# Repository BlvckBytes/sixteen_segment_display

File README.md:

# sixteen_segment_display

## PCB

### display_group

Four sixteen segment displays are considered to be a group.

### interface

The interface board drives a display group by converting the serial signal into all sixteen segments, including the decimal point, as well as each display's enabled state.

### driver

Has yet to be implemented.

The driver board resembles the bridge between modern devices and the display while also handling the process of detecting the total number of displays, handling the character decoding process, multiplexing displays and playing various animations, like blinking letters or scrolling text.

## Software

### SegmentStates

This project encodes all available segment states in order to display various characters. A decoding table is then generated from this information.

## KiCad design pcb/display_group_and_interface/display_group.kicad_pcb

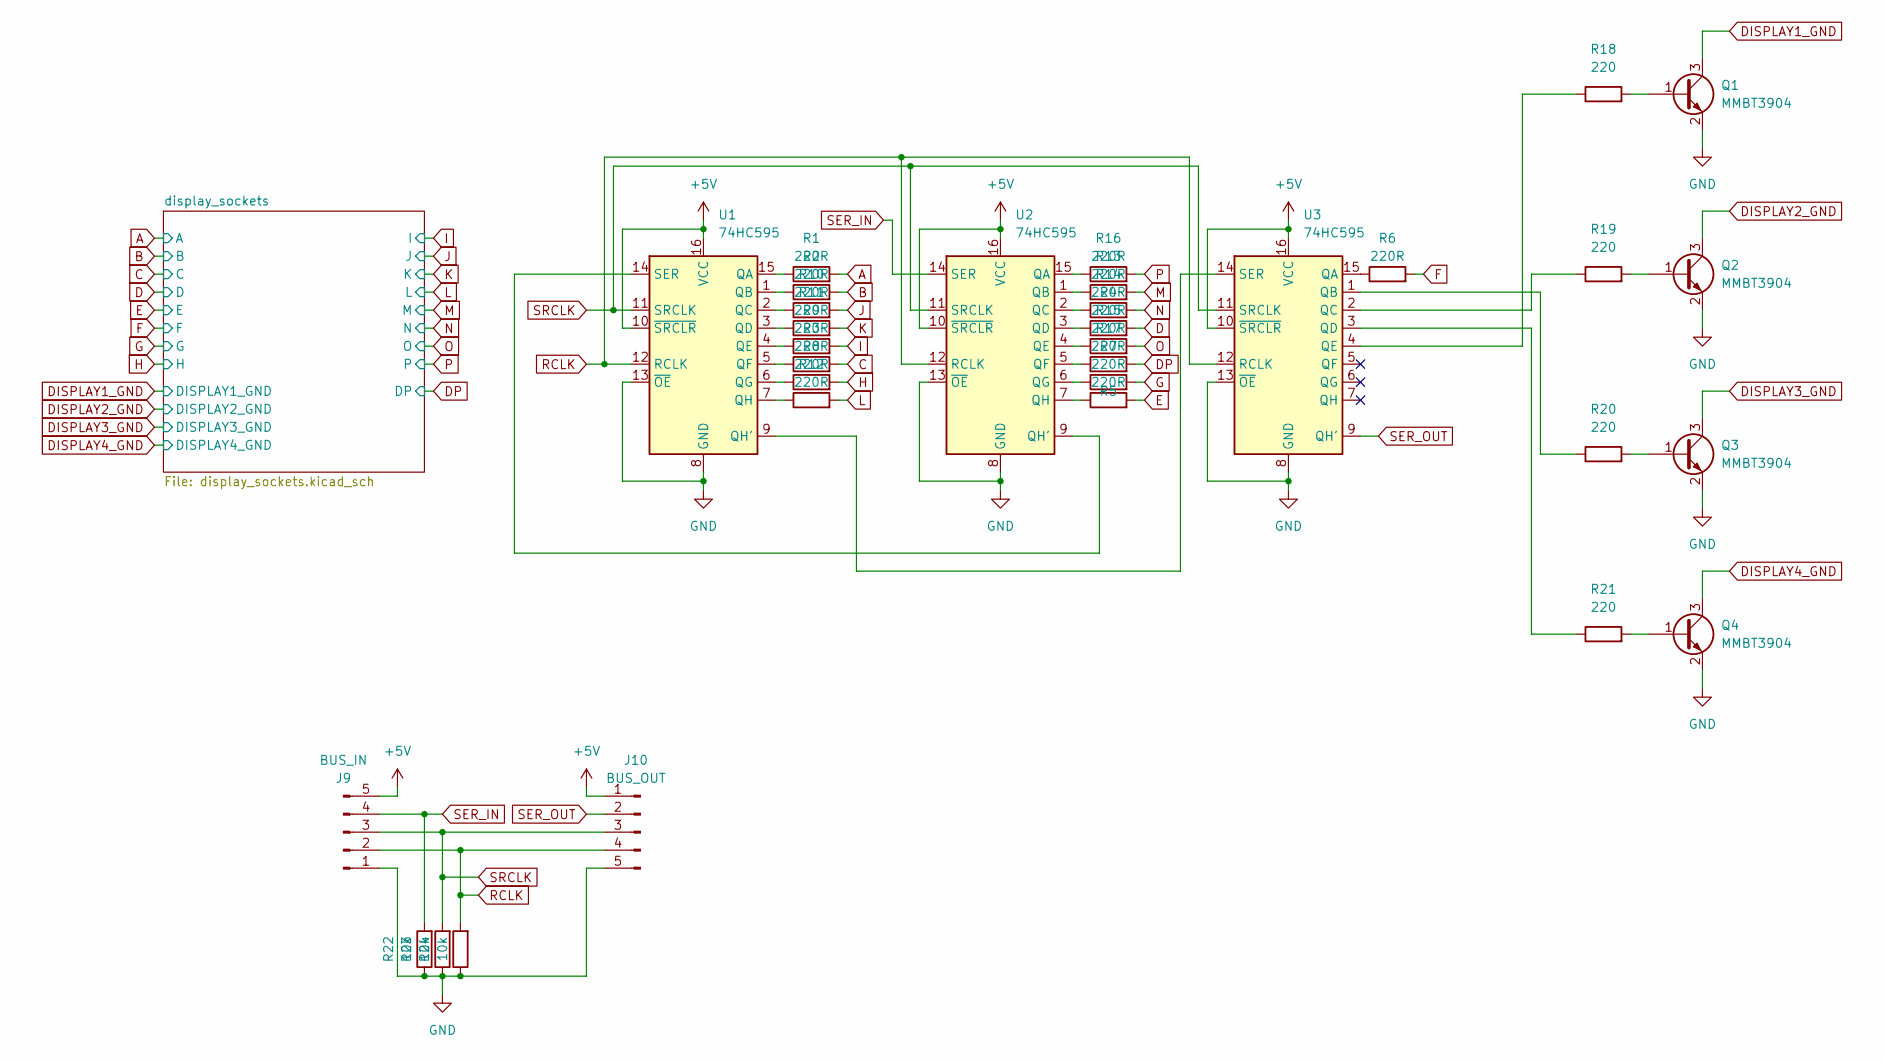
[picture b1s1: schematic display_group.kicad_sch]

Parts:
J9: BUS_IN; PinHeader_01x05_P2.54mm_Horizontal_SMDified
J10: BUS_OUT; PinHeader_01x05_P2.54mm_Horizontal_SMDified
Q1, Q2, Q3, Q4: MMBT3904; SOT-23
R1, R2, R3, R4, R5, R6, R7, R8, R9, R10, R11, R12, R13, R14, R15, R16, R17: 220R; R_0603_1608Metric
R18, R19, R20, R21: 220; R_0603_1608Metric
R22, R23, R24: 10k; R_0603_1608Metric
U1, U2, U3: 74HC595; SOIC-16_3.9x9.9mm_P1.27mm

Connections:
+5V: J9.5, J10.1, U1.10 (~SRCLR), U1.16 (VCC), U2.10 (~SRCLR), U2.16 (VCC), U3.10 (~SRCLR), U3.16 (VCC)
A: R1.2; also elsewhere on the board
B: R2.2; also elsewhere on the board
C: R3.2; also elsewhere on the board
D: R4.2; also elsewhere on the board
DISPLAY1_GND: Q1.3 (C); also elsewhere on the board
DISPLAY2_GND: Q2.3 (C); also elsewhere on the board
DISPLAY3_GND: Q3.3 (C); also elsewhere on the board
DISPLAY4_GND: Q4.3 (C); also elsewhere on the board
DP: R17.2; also elsewhere on the board
E: R5.2; also elsewhere on the board
F: R6.2; also elsewhere on the board
G: R7.2; also elsewhere on the board
GND: J9.1, J10.5, Q1.2 (E), Q2.2 (E), Q3.2 (E), Q4.2 (E), R22.1, R23.1, R24.1, U1.8 (GND), U1.13 (~OE), U2.8 (GND), U2.13 (~OE), U3.8 (GND), U3.13 (~OE)
H: R8.2; also elsewhere on the board
I: R9.2; also elsewhere on the board
J: R10.2; also elsewhere on the board
K: R11.2; also elsewhere on the board
L: R12.2; also elsewhere on the board
M: R13.2; also elsewhere on the board
N: R14.2; also elsewhere on the board
unnamed: Q1.1 (B), R18.2
unnamed: Q2.1 (B), R19.2
unnamed: Q3.1 (B), R20.2
unnamed: Q4.1 (B), R21.2
unnamed: R1.1, U1.15 (QA)
unnamed: R2.1, U1.1 (QB)
unnamed: R10.1, U1.2 (QC)
unnamed: R11.1, U1.3 (QD)
unnamed: R9.1, U1.4 (QE)
unnamed: R3.1, U1.5 (QF)
unnamed: R8.1, U1.6 (QG)
unnamed: U1.9 (QH'), U3.14 (SER)
unnamed: R12.1, U1.7 (QH)
unnamed: U1.14 (SER), U2.9 (QH')
unnamed: R16.1, U2.15 (QA)
unnamed: R13.1, U2.1 (QB)
unnamed: R14.1, U2.2 (QC)
unnamed: R4.1, U2.3 (QD)
unnamed: R15.1, U2.4 (QE)
unnamed: R17.1, U2.5 (QF)
unnamed: R7.1, U2.6 (QG)
unnamed: R5.1, U2.7 (QH)
unnamed: R6.1, U3.15 (QA)
unnamed: R20.1, U3.1 (QB)
unnamed: R19.1, U3.2 (QC)
unnamed: R21.1, U3.3 (QD)
unnamed: R18.1, U3.4 (QE)
O: R15.2; also elsewhere on the board
P: R16.2; also elsewhere on the board
RCLK: J9.2, J10.4, R24.2, U1.12 (RCLK), U2.12 (RCLK), U3.12 (RCLK)
SER_IN: J9.4, R22.2, U2.14 (SER)
SER_OUT: J10.2, U3.9 (QH')
SRCLK: J9.3, J10.3, R23.2, U1.11 (SRCLK), U2.11 (SRCLK), U3.11 (SRCLK)

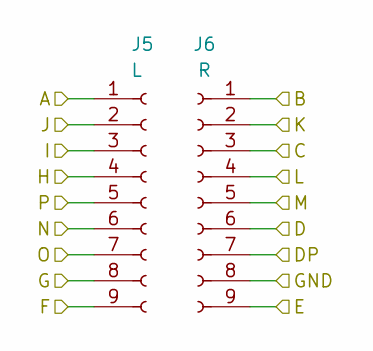
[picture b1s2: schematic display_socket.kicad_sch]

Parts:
J5: L; PinSocket_1x09_P2.54mm_Vertical_SMD_Pin1Right
J6: R; PinSocket_1x09_P2.54mm_Vertical_SMD_Pin1Right

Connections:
A: J5.1; also elsewhere on the board
B: J6.1; also elsewhere on the board
C: J6.3; also elsewhere on the board
D: J6.6; also elsewhere on the board
DISPLAY3_GND: J6.8; also elsewhere on the board
DP: J6.7; also elsewhere on the board
E: J6.9; also elsewhere on the board
F: J5.9; also elsewhere on the board
G: J5.8; also elsewhere on the board
H: J5.4; also elsewhere on the board
I: J5.3; also elsewhere on the board
J: J5.2; also elsewhere on the board
K: J6.2; also elsewhere on the board
L: J6.4; also elsewhere on the board
M: J6.5; also elsewhere on the board
N: J5.6; also elsewhere on the board
O: J5.7; also elsewhere on the board
P: J5.5; also elsewhere on the board

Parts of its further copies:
J1, J3, J7: L; PinSocket_1x09_P2.54mm_Vertical_SMD_Pin1Right
J2, J4, J8: R; PinSocket_1x09_P2.54mm_Vertical_SMD_Pin1Right

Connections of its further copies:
A: J1.1, J3.1, J7.1; also elsewhere on the board
B: J2.1, J4.1, J8.1; also elsewhere on the board
C: J2.3, J4.3, J8.3; also elsewhere on the board
D: J2.6, J4.6, J8.6; also elsewhere on the board
DISPLAY1_GND: J8.8; also elsewhere on the board
DISPLAY2_GND: J2.8; also elsewhere on the board
DISPLAY4_GND: J4.8; also elsewhere on the board
DP: J2.7, J4.7, J8.7; also elsewhere on the board
E: J2.9, J4.9, J8.9; also elsewhere on the board
F: J1.9, J3.9, J7.9; also elsewhere on the board
G: J1.8, J3.8, J7.8; also elsewhere on the board
H: J1.4, J3.4, J7.4; also elsewhere on the board
I: J1.3, J3.3, J7.3; also elsewhere on the board
J: J1.2, J3.2, J7.2; also elsewhere on the board
K: J2.2, J4.2, J8.2; also elsewhere on the board
L: J2.4, J4.4, J8.4; also elsewhere on the board
M: J2.5, J4.5, J8.5; also elsewhere on the board
N: J1.6, J3.6, J7.6; also elsewhere on the board
O: J1.7, J3.7, J7.7; also elsewhere on the board
P: J1.5, J3.5, J7.5; also elsewhere on the board

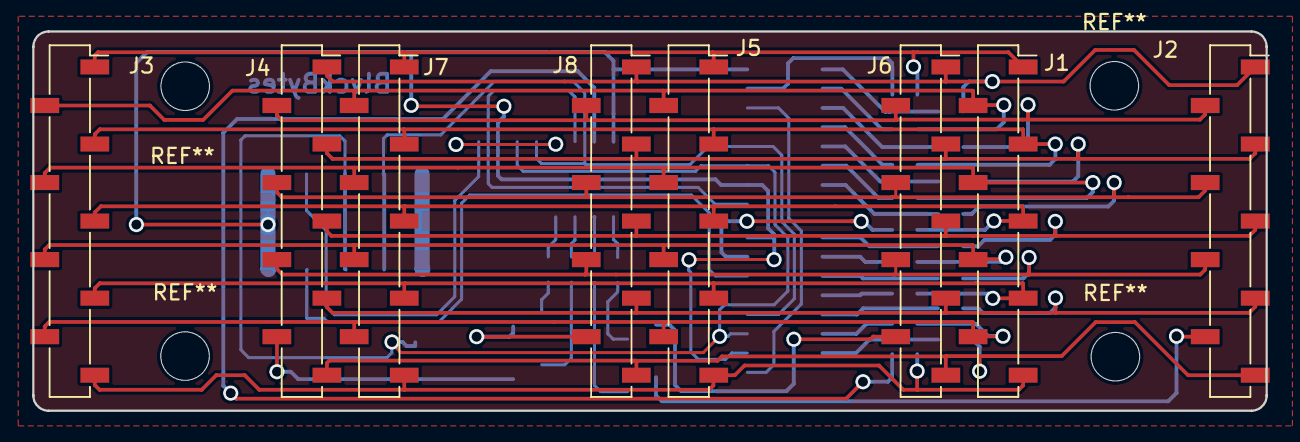
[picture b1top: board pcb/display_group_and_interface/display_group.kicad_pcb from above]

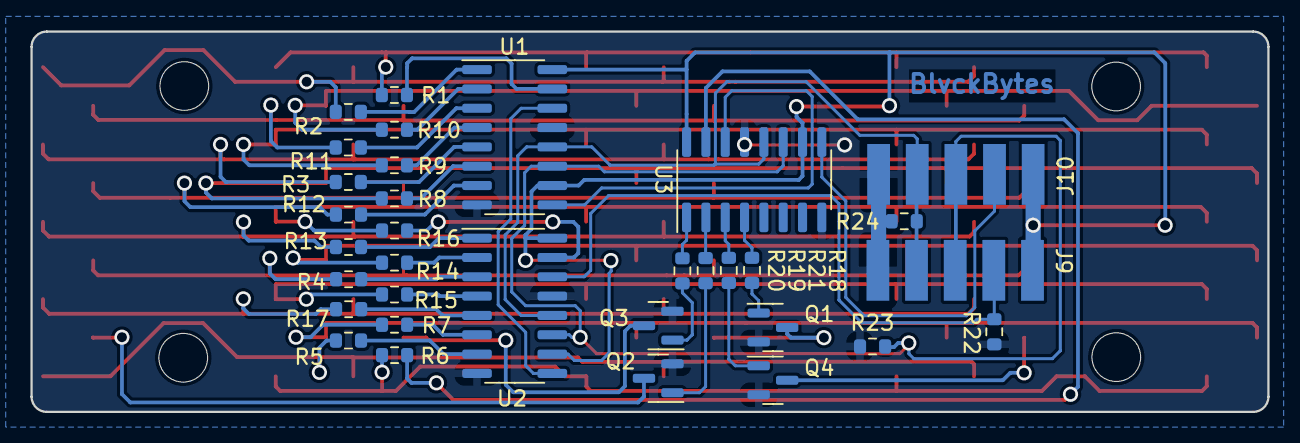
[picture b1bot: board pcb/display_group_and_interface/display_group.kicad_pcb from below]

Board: 2 copper layers, 81.3 x 25.0 mm, 41 parts (33 on the bottom side), 54 nets.

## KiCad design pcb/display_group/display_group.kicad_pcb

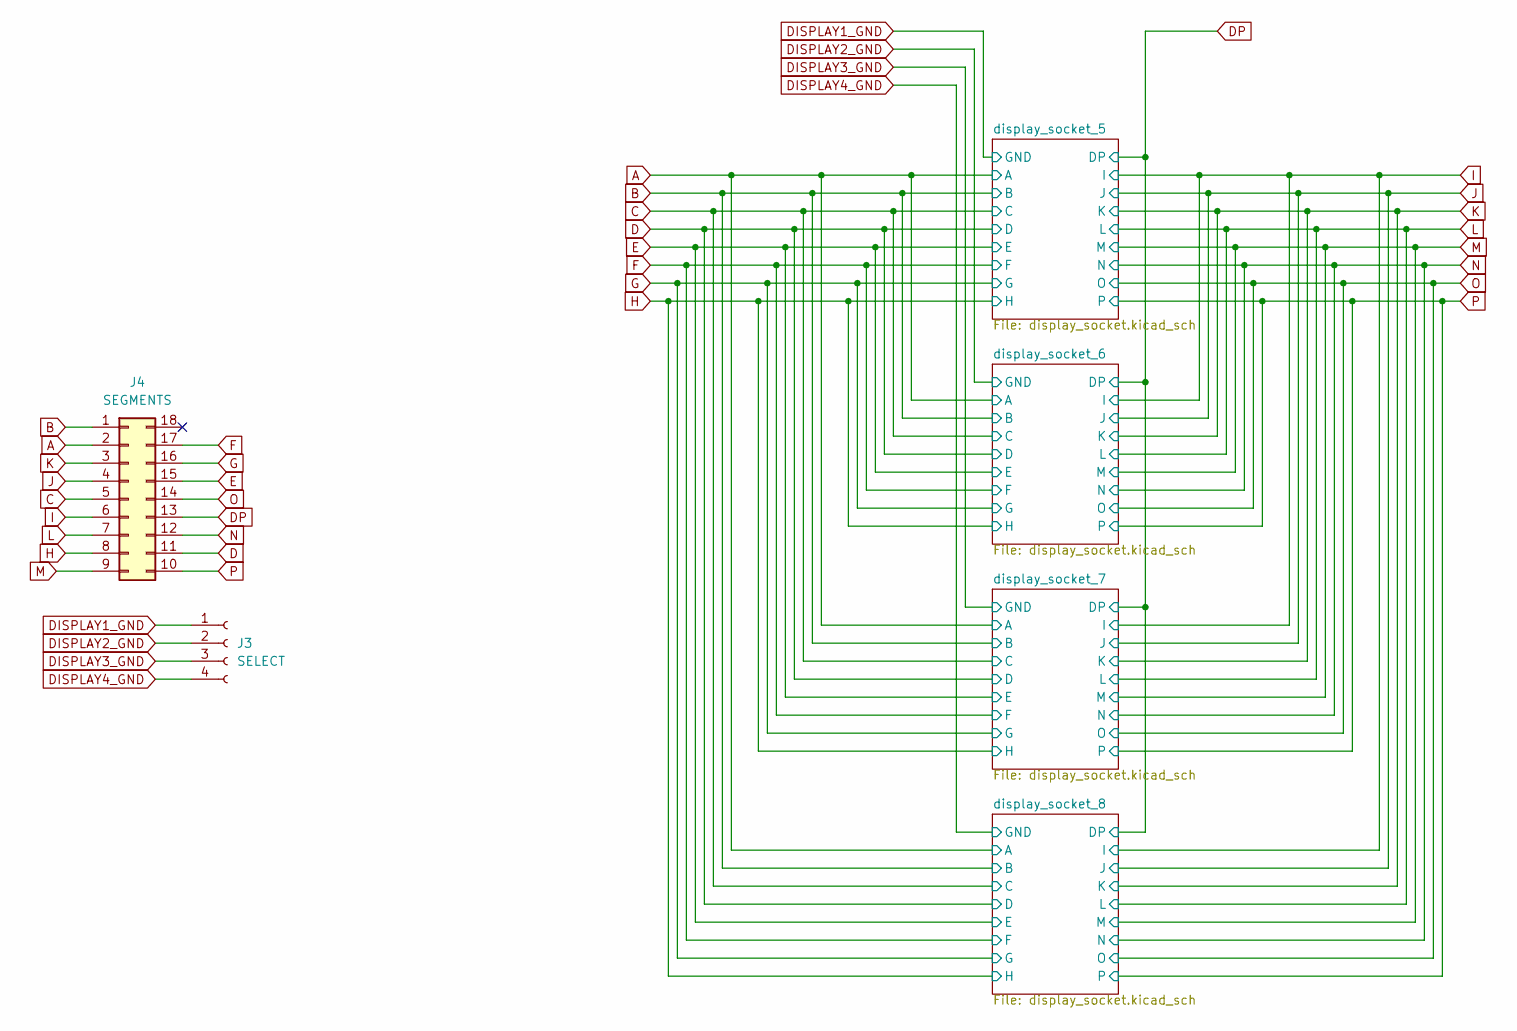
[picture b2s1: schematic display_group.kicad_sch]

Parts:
J3: SELECT; PinSocket_1x04_P2.54mm_Vertical_SMD_Pin1Left
J4: SEGMENTS; PinHeader_2x09_P2.54mm_Vertical

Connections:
A: J4.2; also elsewhere on the board
B: J4.1; also elsewhere on the board
C: J4.5; also elsewhere on the board
D: J4.11; also elsewhere on the board
DISPLAY1_GND: J3.1; also elsewhere on the board
DISPLAY2_GND: J3.2; also elsewhere on the board
DISPLAY3_GND: J3.3; also elsewhere on the board
DISPLAY4_GND: J3.4; also elsewhere on the board
DP: J4.13; also elsewhere on the board
E: J4.15; also elsewhere on the board
F: J4.17; also elsewhere on the board
G: J4.16; also elsewhere on the board
H: J4.8; also elsewhere on the board
I: J4.6; also elsewhere on the board
J: J4.4; also elsewhere on the board
K: J4.3; also elsewhere on the board
L: J4.7; also elsewhere on the board
M: J4.9; also elsewhere on the board
N: J4.12; also elsewhere on the board
O: J4.14; also elsewhere on the board
P: J4.10; also elsewhere on the board

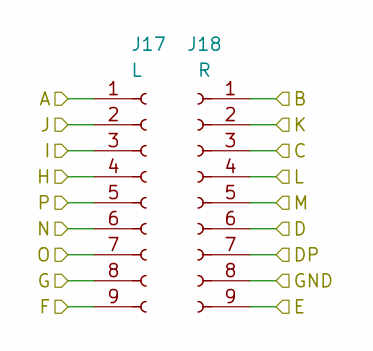
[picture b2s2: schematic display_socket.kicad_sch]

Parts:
J17: L; PinSocket_1x09_P2.54mm_Vertical_SMD_Pin1Right
J18: R; PinSocket_1x09_P2.54mm_Vertical_SMD_Pin1Right

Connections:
A: J17.1; also elsewhere on the board
B: J18.1; also elsewhere on the board
C: J18.3; also elsewhere on the board
D: J18.6; also elsewhere on the board
DISPLAY1_GND: J18.8; also elsewhere on the board
DP: J18.7; also elsewhere on the board
E: J18.9; also elsewhere on the board
F: J17.9; also elsewhere on the board
G: J17.8; also elsewhere on the board
H: J17.4; also elsewhere on the board
I: J17.3; also elsewhere on the board
J: J17.2; also elsewhere on the board
K: J18.2; also elsewhere on the board
L: J18.4; also elsewhere on the board
M: J18.5; also elsewhere on the board
N: J17.6; also elsewhere on the board
O: J17.7; also elsewhere on the board
P: J17.5; also elsewhere on the board

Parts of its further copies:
J1, J5, J7: L; PinSocket_1x09_P2.54mm_Vertical_SMD_Pin1Right
J2, J6, J16: R; PinSocket_1x09_P2.54mm_Vertical_SMD_Pin1Right

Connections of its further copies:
A: J1.1, J5.1, J7.1; also elsewhere on the board
B: J2.1, J6.1, J16.1; also elsewhere on the board
C: J2.3, J6.3, J16.3; also elsewhere on the board
D: J2.6, J6.6, J16.6; also elsewhere on the board
DISPLAY2_GND: J16.8; also elsewhere on the board
DISPLAY3_GND: J6.8; also elsewhere on the board
DISPLAY4_GND: J2.8; also elsewhere on the board
DP: J2.7, J6.7, J16.7; also elsewhere on the board
E: J2.9, J6.9, J16.9; also elsewhere on the board
F: J1.9, J5.9, J7.9; also elsewhere on the board
G: J1.8, J5.8, J7.8; also elsewhere on the board
H: J1.4, J5.4, J7.4; also elsewhere on the board
I: J1.3, J5.3, J7.3; also elsewhere on the board
J: J1.2, J5.2, J7.2; also elsewhere on the board
K: J2.2, J6.2, J16.2; also elsewhere on the board
L: J2.4, J6.4, J16.4; also elsewhere on the board
M: J2.5, J6.5, J16.5; also elsewhere on the board
N: J1.6, J5.6, J7.6; also elsewhere on the board
O: J1.7, J5.7, J7.7; also elsewhere on the board
P: J1.5, J5.5, J7.5; also elsewhere on the board

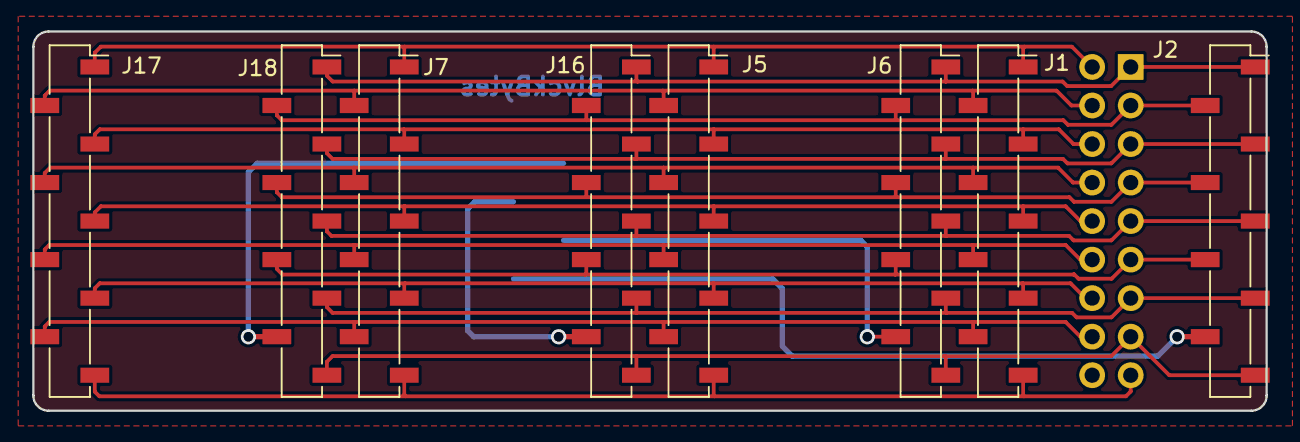
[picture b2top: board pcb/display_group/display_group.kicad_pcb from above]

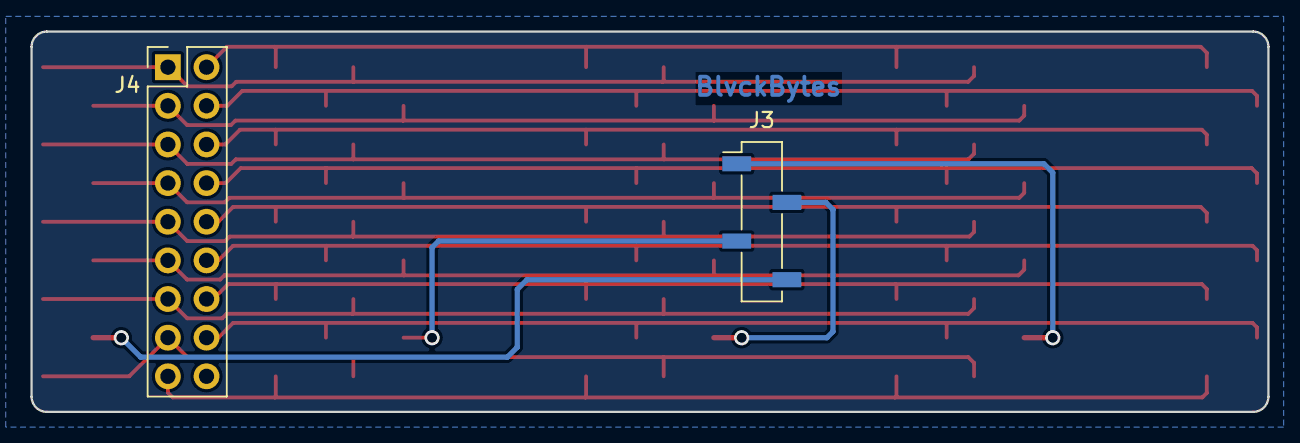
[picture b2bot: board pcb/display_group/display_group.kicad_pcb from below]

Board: 2 copper layers, 81.3 x 25.0 mm, 10 parts (2 on the bottom side), 21 nets.

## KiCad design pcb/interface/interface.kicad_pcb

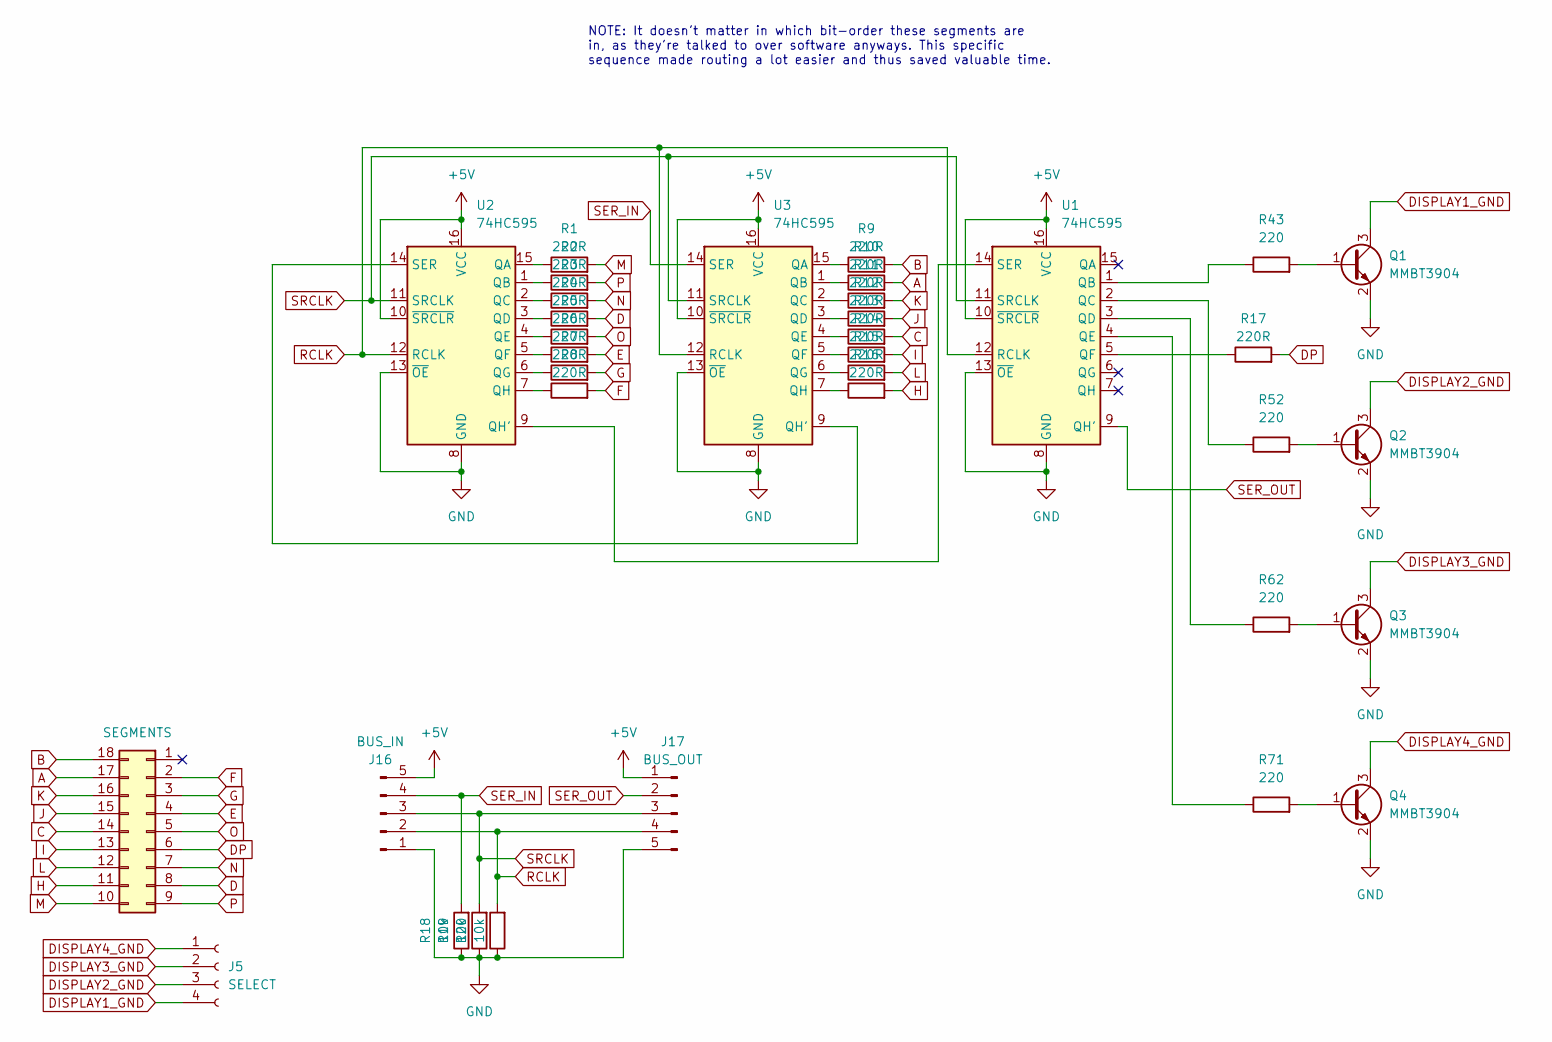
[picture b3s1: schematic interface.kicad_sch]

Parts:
J1: SEGMENTS; PinSocket_2x09_P2.54mm_Vertical
J5: SELECT; PinHeader_1x04_P2.54mm_Vertical
J16: BUS_IN; PinHeader_01x05_P2.54mm_Horizontal_SMDified
J17: BUS_OUT; PinHeader_01x05_P2.54mm_Horizontal_SMDified
Q1, Q2, Q3, Q4: MMBT3904; SOT-23
R1, R2, R3, R4, R5, R6, R7, R8, R9, R10, R11, R12, R13, R14, R15, R16, R17: 220R; R_0603_1608Metric
R18, R19, R20: 10k; R_0603_1608Metric
R43, R52, R62, R71: 220; R_0603_1608Metric
U1, U2, U3: 74HC595; SOIC-16_3.9x9.9mm_P1.27mm

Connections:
+5V: J16.5, J17.1, U1.10 (~SRCLR), U1.16 (VCC), U2.10 (~SRCLR), U2.16 (VCC), U3.10 (~SRCLR), U3.16 (VCC)
A: J1.17, R10.2
B: J1.18, R9.2
C: J1.14, R13.2
D: J1.8, R4.2
DISPLAY1_GND: J5.4, Q1.3 (C)
DISPLAY2_GND: J5.3, Q2.3 (C)
DISPLAY3_GND: J5.2, Q3.3 (C)
DISPLAY4_GND: J5.1, Q4.3 (C)
DP: J1.6, R17.2
E: J1.4, R6.2
F: J1.2, R8.2
G: J1.3, R7.2
GND: J16.1, J17.5, Q1.2 (E), Q2.2 (E), Q3.2 (E), Q4.2 (E), R18.1, R19.1, R20.1, U1.8 (GND), U1.13 (~OE), U2.8 (GND), U2.13 (~OE), U3.8 (GND), U3.13 (~OE)
H: J1.11, R16.2
I: J1.13, R14.2
J: J1.15, R12.2
K: J1.16, R11.2
L: J1.12, R15.2
M: J1.10, R1.2
N: J1.7, R3.2
unnamed: Q1.1 (B), R43.2
unnamed: Q2.1 (B), R52.2
unnamed: Q3.1 (B), R62.2
unnamed: Q4.1 (B), R71.2
unnamed: R43.1, U1.1 (QB)
unnamed: R52.1, U1.2 (QC)
unnamed: R62.1, U1.3 (QD)
unnamed: R71.1, U1.4 (QE)
unnamed: R17.1, U1.5 (QF)
unnamed: U1.14 (SER), U2.9 (QH')
unnamed: R1.1, U2.15 (QA)
unnamed: R2.1, U2.1 (QB)
unnamed: R3.1, U2.2 (QC)
unnamed: R4.1, U2.3 (QD)
unnamed: R5.1, U2.4 (QE)
unnamed: R6.1, U2.5 (QF)
unnamed: R7.1, U2.6 (QG)
unnamed: R8.1, U2.7 (QH)
unnamed: U2.14 (SER), U3.9 (QH')
unnamed: R9.1, U3.15 (QA)
unnamed: R10.1, U3.1 (QB)
unnamed: R11.1, U3.2 (QC)
unnamed: R12.1, U3.3 (QD)
unnamed: R13.1, U3.4 (QE)
unnamed: R14.1, U3.5 (QF)
unnamed: R15.1, U3.6 (QG)
unnamed: R16.1, U3.7 (QH)
O: J1.5, R5.2
P: J1.9, R2.2
RCLK: J16.2, J17.4, R20.2, U1.12 (RCLK), U2.12 (RCLK), U3.12 (RCLK)
SER_IN: J16.4, R18.2, U3.14 (SER)
SER_OUT: J17.2, U1.9 (QH')
SRCLK: J16.3, J17.3, R19.2, U1.11 (SRCLK), U2.11 (SRCLK), U3.11 (SRCLK)

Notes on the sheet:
NOTE: It doesn't matter in which bit-order these segments are in, as they're talked to over software anyways. This specific sequence made routing a lot easier and thus saved valuable time.

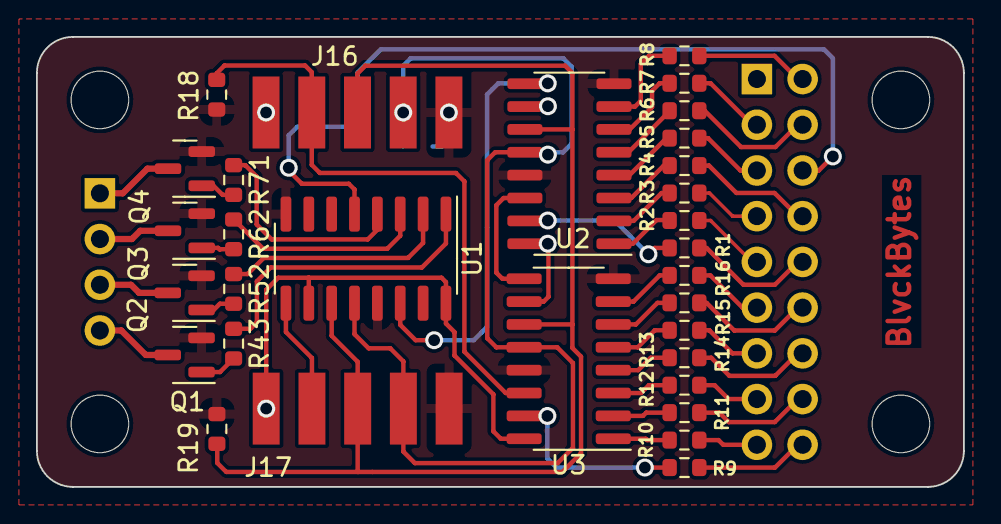
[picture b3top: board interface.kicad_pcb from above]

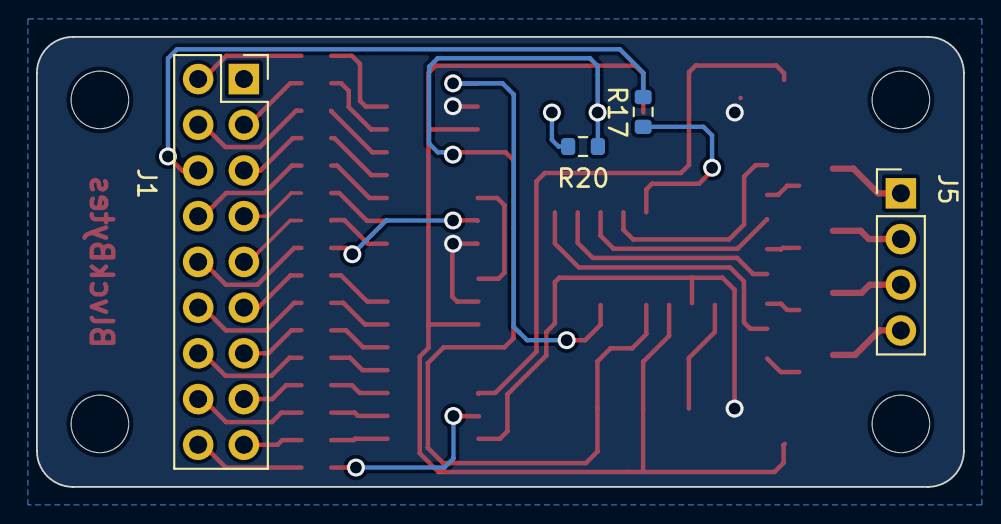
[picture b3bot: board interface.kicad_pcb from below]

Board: 2 copper layers, 51.5 x 25.0 mm, 35 parts (4 on the bottom side), 54 nets.

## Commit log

2023-12-30 cleaned up, reworked and (so far) finalized the interface board
2023-12-30 added missing resistors to the interface board
2023-12-30 cleaned up, reworked and (so far) finalized the display-group board
2023-12-30 increased ground trace width from .25 to .35
2023-12-31 added missing input pulldown resistors to the interface board
2024-01-01 added name embossing to the display_group board
2024-01-01 added the display_group_and_interface board
